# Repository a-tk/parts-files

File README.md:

# parts-files
A place to store project files and to make those available to the world

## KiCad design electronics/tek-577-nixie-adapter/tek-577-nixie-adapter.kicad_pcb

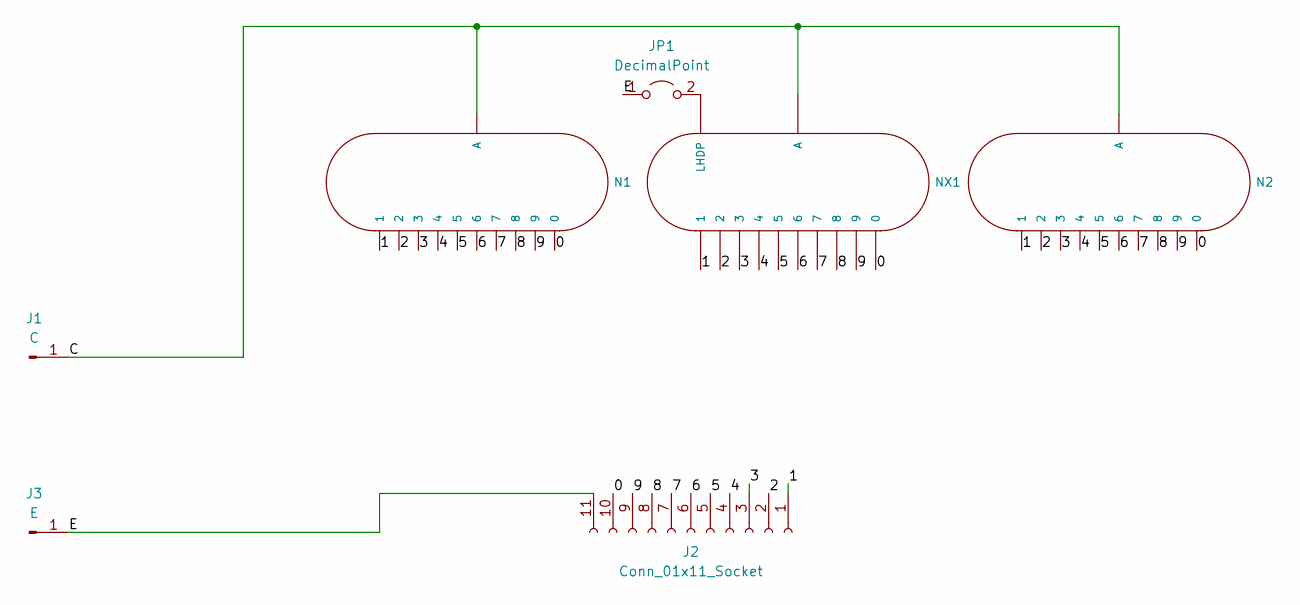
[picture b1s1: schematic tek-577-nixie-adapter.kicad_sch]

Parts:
J1: C; MountingHole_4mm_Pad_TopBottom
J2: Conn_01x11_Socket; Grayhill Single Pole 10 Position Switch
J3: E; MountingHole_4mm_Pad_TopBottom
JP1: DecimalPoint; TestPoint_2Pads_Pitch2.54mm_Drill0.8mm
N1: IN-4; IN-4-DSUB
N2: IN-2; IN-2-DSUB
NX1: IN-12BIN-12-DSUB; IN-12-DSUB

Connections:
/0: J2.10, N1.0, N2.0, NX1.0
/1: J2.1, N1.1, N2.1, NX1.1
/2: J2.2, N1.2, N2.2, NX1.2
/3: J2.3, N1.3, N2.3, NX1.3
/4: J2.4, N1.4, N2.4, NX1.4
/5: J2.5, N1.5, N2.5, NX1.5
/6: J2.6, N1.6, N2.6, NX1.6
/7: J2.7, N1.7, N2.7, NX1.7
/8: J2.8, N1.8, N2.8, NX1.8
/9: J2.9, N1.9, N2.9, NX1.9
/C: J1.1, N1.A3 (A), N2.A, NX1.A
/E: J2.11, J3.1, JP1.1 (A)
unnamed: JP1.2 (B), NX1.LHDP

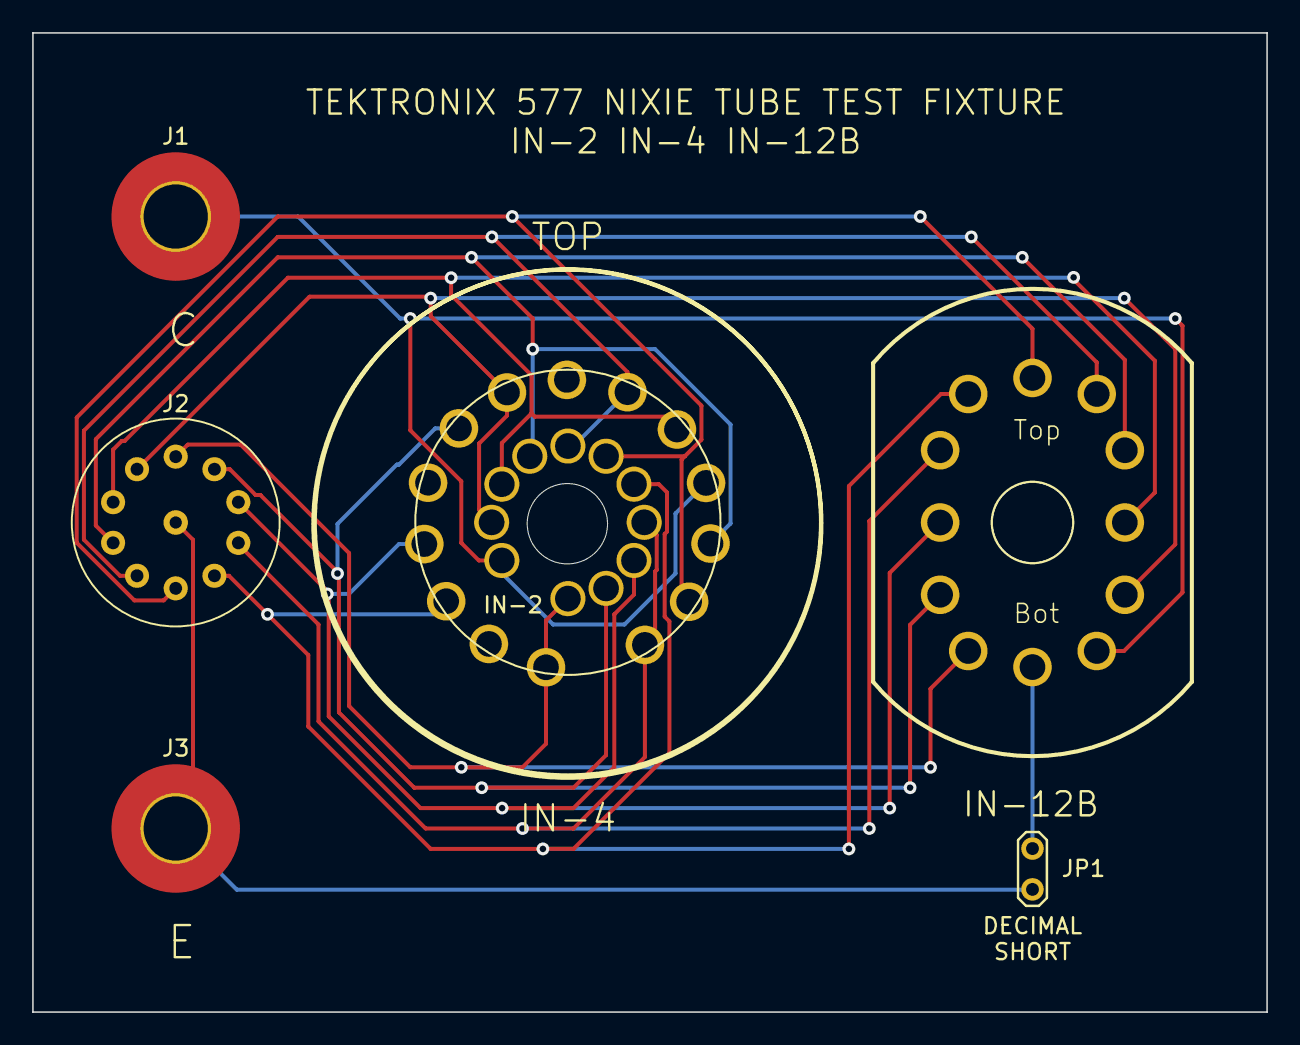
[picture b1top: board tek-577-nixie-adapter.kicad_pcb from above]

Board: 2 copper layers, 76.8 x 61.0 mm, 7 parts (0 on the bottom side), 13 nets.

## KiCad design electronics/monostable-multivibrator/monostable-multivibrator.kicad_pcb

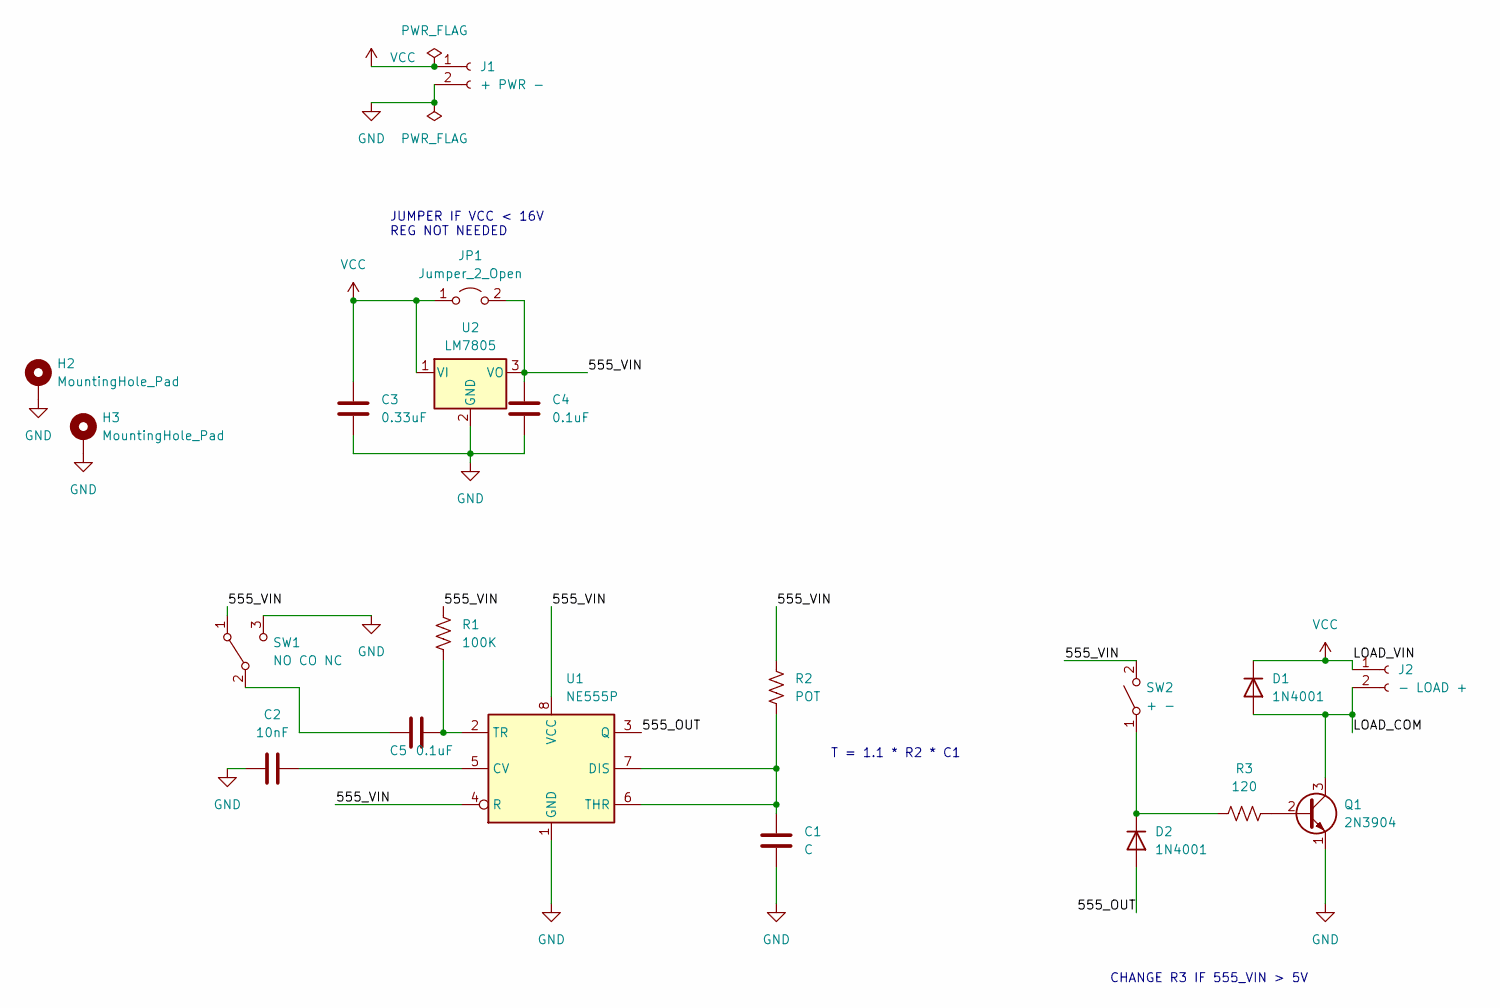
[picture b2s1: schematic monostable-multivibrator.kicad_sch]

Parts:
C1: C; CP_Radial_D8.0mm_P3.80mm
C2: 10nF; C_Disc_D4.3mm_W1.9mm_P5.00mm
C3: 0.33uF; C_Disc_D4.3mm_W1.9mm_P5.00mm
C4, C5: 0.1uF; C_Disc_D4.3mm_W1.9mm_P5.00mm
D1, D2: 1N4001; D_DO-41_SOD81_P10.16mm_Horizontal
H2, H3: MountingHole_Pad; MountingHole_3.2mm_M3_DIN965_Pad_TopBottom
J1: + PWR -; PinSocket_1x02_P2.54mm_Vertical
J2: - LOAD +; PinSocket_1x02_P2.54mm_Vertical
JP1: Jumper_2_Open; R_Axial_DIN0207_L6.3mm_D2.5mm_P2.54mm_Vertical
Q1: 2N3904; TO-92
R1: 100K; R_Axial_DIN0207_L6.3mm_D2.5mm_P7.62mm_Horizontal
R2: POT; R_Axial_DIN0207_L6.3mm_D2.5mm_P7.62mm_Horizontal
R3: 120; R_Axial_DIN0207_L6.3mm_D2.5mm_P7.62mm_Horizontal
SW1: NO CO NC; PinHeader_1x03_P2.54mm_Vertical
SW2: + -; PinHeader_1x02_P2.54mm_Vertical
U1: NE555P; DIP-8_W7.62mm
U2: LM7805; TO-220-3_Vertical

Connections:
/555_OUT: D2.2 (A), U1.3 (Q)
/555_VIN: C4.1, JP1.2 (B), R1.1, R2.1, SW1.1 (A), SW2.2 (B), U1.4 (R), U1.8 (VCC), U2.3 (VO)
/LOAD_COM: D1.2 (A), J2.2, Q1.3 (C)
GND: C1.2, C2.1, C3.2, C4.2, H2.1, H3.1, J1.2, Q1.1 (E), SW1.3 (C), U1.1 (GND), U2.2 (GND)
unnamed: D2.1 (K), R3.1, SW2.1 (A)
unnamed: Q1.2 (B), R3.2
unnamed: C5.2, SW1.2 (B)
unnamed: C2.2, U1.5 (CV)
unnamed: C1.1, R2.2, U1.6 (THR), U1.7 (DIS)
unnamed: C5.1, R1.2, U1.2 (TR)
VCC: C3.1, D1.1 (K), J1.1, J2.1, JP1.1 (A), U2.1 (VI)

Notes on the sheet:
CHANGE R3 IF 555_VIN > 5V
JUMPER IF VCC < 16V REG NOT NEEDED
T = 1.1 * R2 * C1

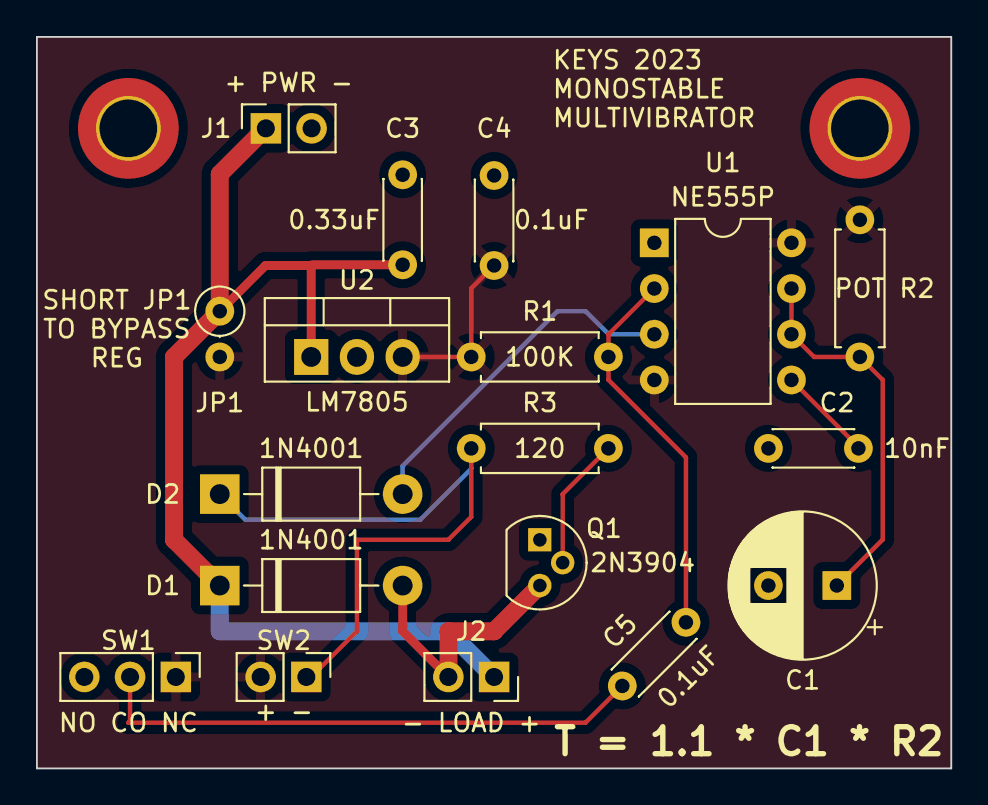
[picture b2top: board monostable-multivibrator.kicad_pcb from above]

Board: 2 copper layers, 50.8 x 40.6 mm, 20 parts (0 on the bottom side), 11 nets.

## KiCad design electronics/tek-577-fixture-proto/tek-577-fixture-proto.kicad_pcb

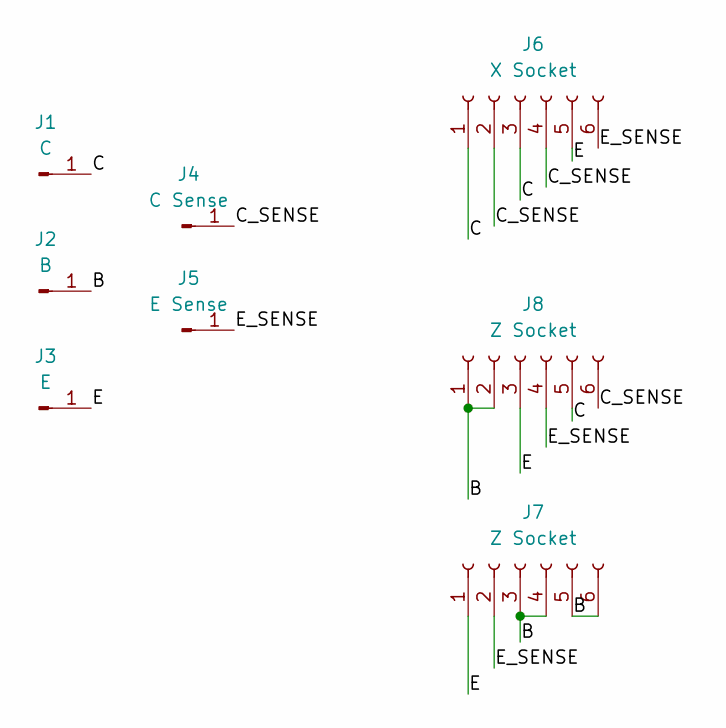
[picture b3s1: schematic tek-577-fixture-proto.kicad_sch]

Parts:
J1: C; MountingHole_4mm_Pad_TopBottom
J2: B; MountingHole_4mm_Pad_TopBottom
J3: E; MountingHole_4mm_Pad_TopBottom
J4: C Sense; MountingHole_4mm_Pad_TopBottom
J5: E Sense; MountingHole_4mm_Pad_TopBottom
J6: X Socket; PinSocket_1x06_P2.54mm_Vertical
J7, J8: Z Socket; PinSocket_1x06_P2.54mm_Vertical

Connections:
/B: J2.1, J7.3, J7.4, J7.5, J7.6, J8.1, J8.2
/C: J1.1, J6.1, J6.3, J8.5
/C_SENSE: J4.1, J6.2, J6.4, J8.6
/E: J3.1, J6.5, J7.1, J8.3
/E_SENSE: J5.1, J6.6, J7.2, J8.4

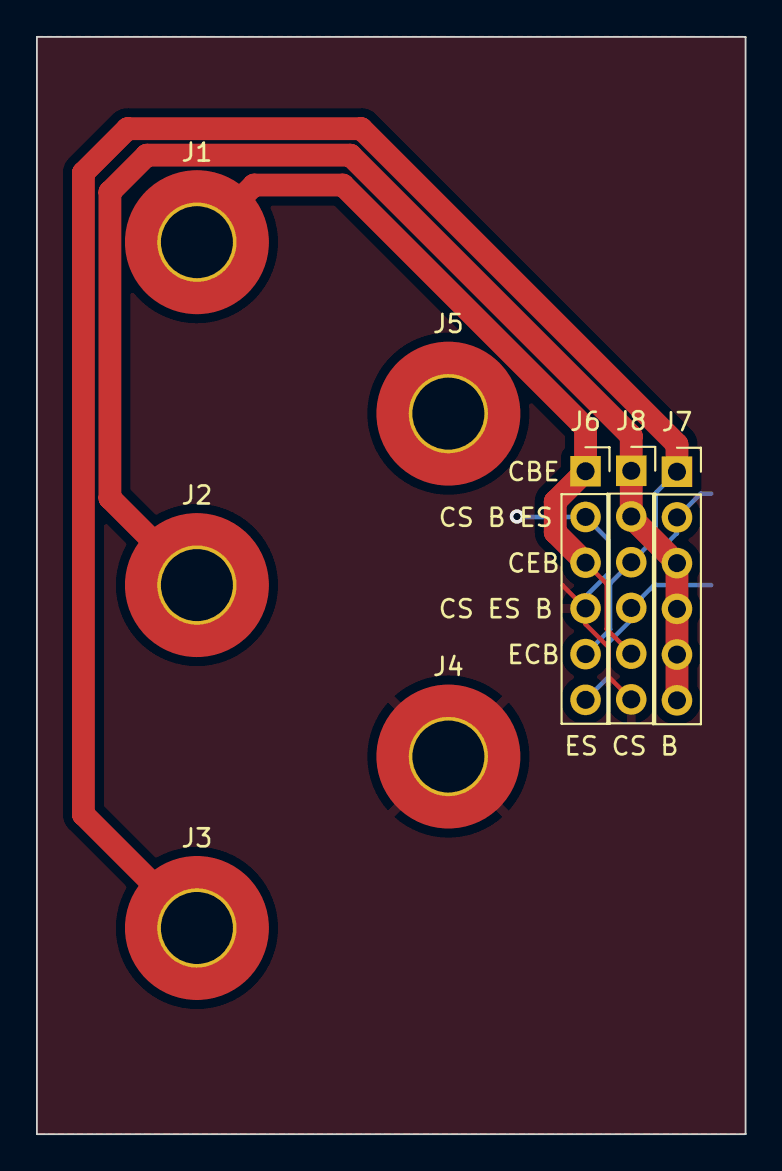
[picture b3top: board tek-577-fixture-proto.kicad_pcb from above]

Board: 2 copper layers, 39.4 x 61.0 mm, 8 parts (0 on the bottom side), 5 nets.

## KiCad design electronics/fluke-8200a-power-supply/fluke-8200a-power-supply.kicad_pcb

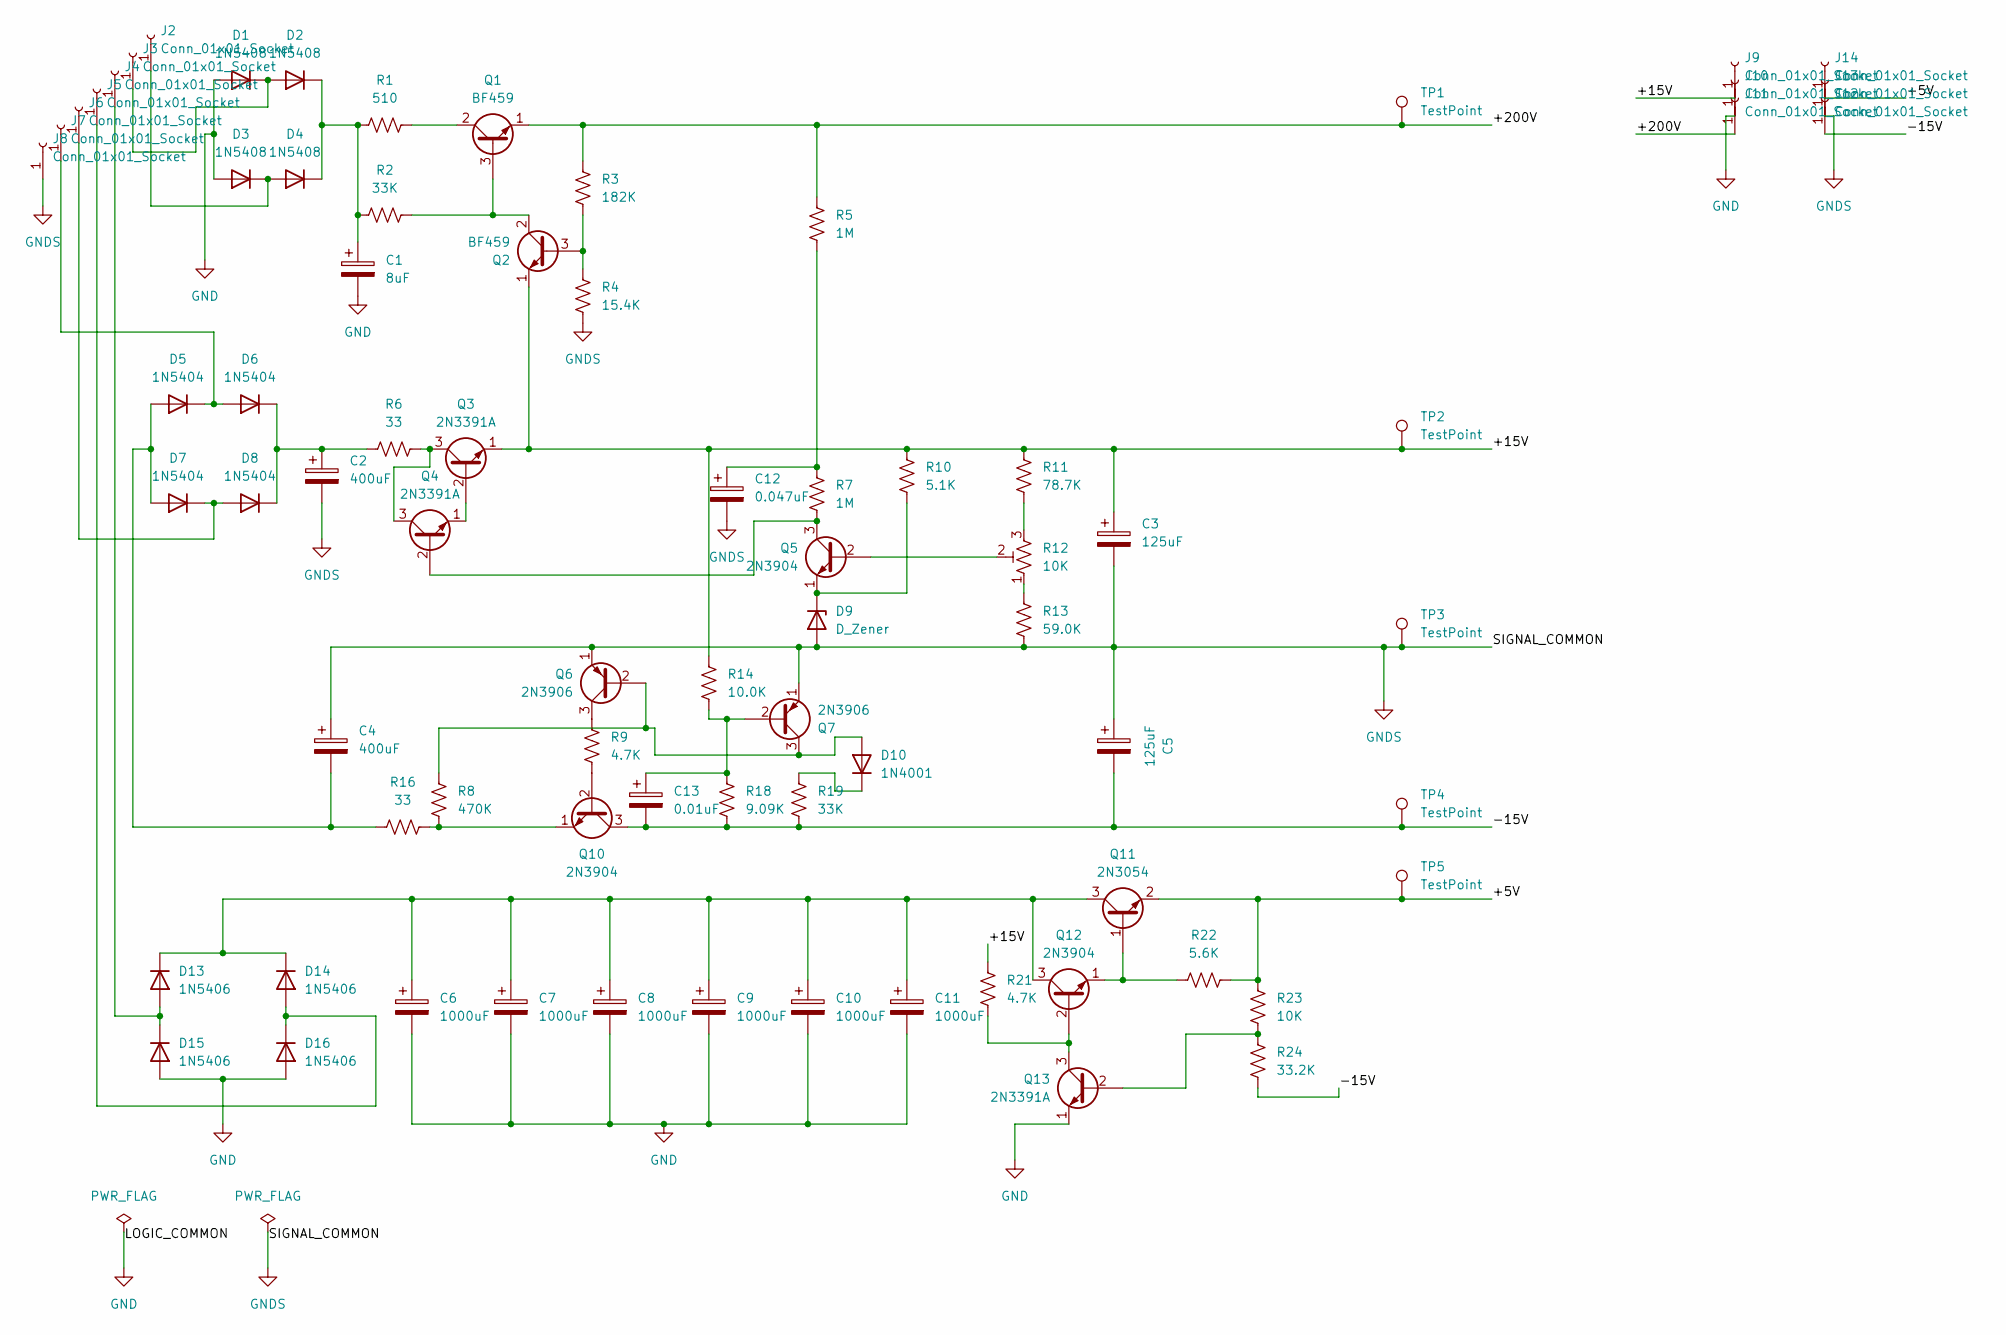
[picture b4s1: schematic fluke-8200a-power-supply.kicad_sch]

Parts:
C1: 8uF; CP_Axial_L37.0mm_D13.0mm_P43.00mm_Horizontal
C2, C4: 400uF; CP_Axial_L30.0mm_D10.0mm_P35.00mm_Horizontal
C3, C5: 125uF; CP_Axial_L18.0mm_D8.0mm_P25.00mm_Horizontal
C6, C7, C8, C9, C10, C11: 1000uF; CP_Axial_L30.0mm_D10.0mm_P35.00mm_Horizontal
C12: 0.047uF; C_Rect_L13.0mm_W4.0mm_P10.00mm_FKS3_FKP3_MKS4
C13: 0.01uF; C_Disc_D8.0mm_W2.5mm_P5.00mm
D1, D2, D3, D4: 1N5408; D_DO-201AD_P15.24mm_Horizontal
D5, D6, D7, D8: 1N5404; D_DO-201AD_P15.24mm_Horizontal
D9: D_Zener; D_A-405_P12.70mm_Horizontal
D10: 1N4001; D_DO-41_SOD81_P12.70mm_Horizontal
D13, D14, D15, D16: 1N5406; D_DO-201AD_P15.24mm_Horizontal
J2, J3, J4, J5, J6, J7, J8, J9, J10, J11, J12, J13, J14: Conn_01x01_Socket; PinSocket_1x01_P2.54mm_Vertical
Q1, Q2: BF459; TO-126-3_Vertical
Q3, Q4, Q13: 2N3391A; TO-92_Inline
Q5, Q10, Q12: 2N3904; TO-92_Inline
Q6, Q7: 2N3906; TO-92_Inline
Q11: 2N3054; TO66
R1: 510; R_Axial_DIN0614_L14.3mm_D5.7mm_P15.24mm_Horizontal
R2, R19: 33K; R_Axial_DIN0309_L9.0mm_D3.2mm_P12.70mm_Horizontal
R3: 182K; R_Axial_DIN0309_L9.0mm_D3.2mm_P12.70mm_Horizontal
R4: 15.4K; R_Axial_DIN0309_L9.0mm_D3.2mm_P12.70mm_Horizontal
R5, R7: 1M; R_Axial_DIN0309_L9.0mm_D3.2mm_P12.70mm_Horizontal
R6, R16: 33; R_Axial_DIN0309_L9.0mm_D3.2mm_P12.70mm_Horizontal
R8: 470K; R_Axial_DIN0309_L9.0mm_D3.2mm_P12.70mm_Horizontal
R9, R21: 4.7K; R_Axial_DIN0309_L9.0mm_D3.2mm_P12.70mm_Horizontal
R10: 5.1K; R_Axial_DIN0309_L9.0mm_D3.2mm_P12.70mm_Horizontal
R11: 78.7K; R_Axial_DIN0309_L9.0mm_D3.2mm_P12.70mm_Horizontal
R12: 10K; Potentiometer_Runtron_RM-063_Horizontal
R13: 59.0K; R_Axial_DIN0309_L9.0mm_D3.2mm_P12.70mm_Horizontal
R14: 10.0K; R_Axial_DIN0309_L9.0mm_D3.2mm_P12.70mm_Horizontal
R18: 9.09K; R_Axial_DIN0309_L9.0mm_D3.2mm_P12.70mm_Horizontal
R22: 5.6K; R_Axial_DIN0309_L9.0mm_D3.2mm_P12.70mm_Horizontal
R23: 10K; R_Axial_DIN0309_L9.0mm_D3.2mm_P12.70mm_Horizontal
R24: 33.2K; R_Axial_DIN0309_L9.0mm_D3.2mm_P12.70mm_Horizontal
TP1, TP2, TP3, TP4, TP5: TestPoint; TestPoint_Loop_D3.50mm_Drill0.9mm_Beaded

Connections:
/+5V: J14.1, Q11.2 (E), R22.2, R23.2, TP5.1
/+15V: C3.1, J9.1, Q2.1 (E), Q3.1 (E), R10.1, R11.1, R14.1, R21.2, TP2.1
/+200V: J11.1, Q1.1 (E), R3.2, R5.1, TP1.1
/-15V: C5.2, C13.2, J12.1, Q10.3 (C), R18.1, R19.1, R24.1, TP4.1
GND: C1.2, C6.2, C7.2, C8.2, C9.2, C10.2, C11.2, D1.2 (A), D3.2 (A), D15.2 (A), D16.2 (A), J10.1, Q13.1 (E)
GNDS: C2.2, C3.2, C4.1, C5.1, C12.2, D9.2 (A), J8.1, J13.1, Q6.1 (E), Q7.1 (E), R4.1, R13.2, TP3.1
unnamed: C12.1, R5.2, R7.1
unnamed: D1.1 (K), D2.2 (A), J3.1
unnamed: C1.1, D2.1 (K), D4.1 (K), R1.1, R2.1
unnamed: D3.1 (K), D4.2 (A), J2.1
unnamed: C4.2, D5.2 (A), D7.2 (A), R16.1
unnamed: D5.1 (K), D6.2 (A), J7.1
unnamed: C2.1, D6.1 (K), D8.1 (K), R6.1
unnamed: D7.1 (K), D8.2 (A), J6.1
unnamed: D9.1 (K), Q5.1 (E), R10.2
unnamed: D10.2 (A), Q6.2 (B), Q7.3 (C), R8.1
unnamed: D10.1 (K), R19.2
unnamed: D13.2 (A), D15.1 (K), J4.1
unnamed: C6.1, C7.1, C8.1, C9.1, C10.1, C11.1, D13.1 (K), D14.1 (K), Q11.3 (C), Q12.3 (C)
unnamed: D14.2 (A), D16.1 (K), J5.1
unnamed: Q1.3 (B), Q2.2 (C), R2.2
unnamed: Q1.2 (C), R1.2
unnamed: Q2.3 (B), R3.1, R4.2
unnamed: Q3.2 (B), Q4.1 (E)
unnamed: Q3.3 (C), Q4.3 (C), R6.2
unnamed: Q4.2 (B), Q5.3 (C), R7.2
unnamed: Q5.2 (B), R12.2
unnamed: Q6.3 (C), R9.1
unnamed: C13.1, Q7.2 (B), R14.2, R18.2
unnamed: Q10.2 (B), R9.2
unnamed: Q10.1 (E), R8.2, R16.2
unnamed: Q11.1 (B), Q12.1 (E), R22.1
unnamed: Q12.2 (B), Q13.3 (C), R21.1
unnamed: Q13.2 (B), R23.1, R24.2
unnamed: R11.2, R12.3
unnamed: R12.1, R13.1

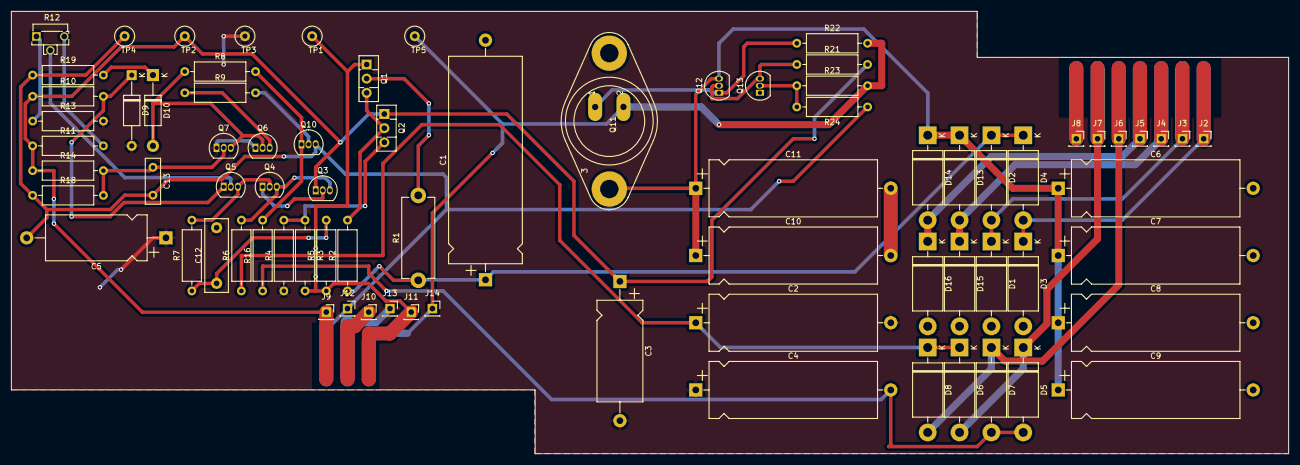
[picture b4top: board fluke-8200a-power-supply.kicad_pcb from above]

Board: 2 copper layers, 229.2 x 79.4 mm, 77 parts (0 on the bottom side), 36 nets.

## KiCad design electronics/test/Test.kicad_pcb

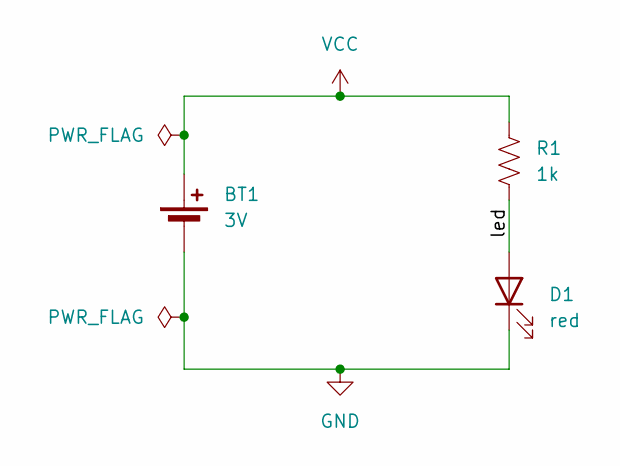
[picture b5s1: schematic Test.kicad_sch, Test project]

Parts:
BT1: 3V; BatteryHolder_Keystone_1058_1x2032
D1: red; LED_D5.0mm
R1: 1k; R_Axial_DIN0309_L9.0mm_D3.2mm_P12.70mm_Horizontal

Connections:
/led: D1.2 (A), R1.2
GND: BT1.2 (-), D1.1 (K)
VCC: BT1.1 (+), R1.1

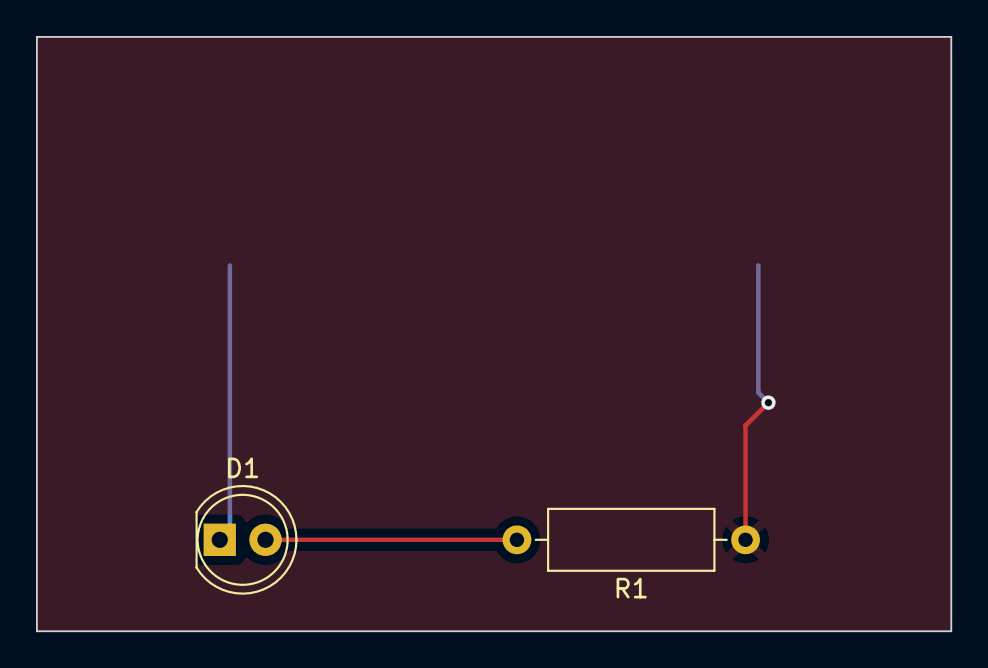
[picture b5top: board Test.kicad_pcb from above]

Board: 2 copper layers, 50.8 x 33.0 mm, 3 parts (1 on the bottom side), 3 nets.

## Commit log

2023-03-16 Adding directory
2023-04-13 Adding drawing for Shars conversion
2023-06-10 adding electonics file and basic kicad project
2023-06-11 adding tutorial directory
2023-06-11 finished tutorial
2023-06-11 adding basic schematic
2023-06-11 adding more components
2023-06-11 more updates
2023-06-11 mostly finished
2023-06-12 footprints
2023-06-12 adjustments
2023-06-12 looking finished
2023-06-13 adding important note
2023-06-13 adding test project. Abandoning this method, moving to schematic match
2023-06-13 only need correct transistors now
2023-06-13 changed to pin headers
2023-06-13 PCB work.
2023-06-14 PCB quotable, but not yet fully compatable with fluke 8200A
2023-06-15 adding new project
2023-06-21 boilerplate
2023-06-21 adding symbols
2023-06-21 working footprints
2023-06-22 adding library references and cleanup
2023-06-22 adding other tubes
2023-06-22 adding switch and schematic done
2023-06-22 adding the footprints, which only loaded on mac for some reason
2023-06-22 board design done
2023-06-22 routing improvements
2023-06-25 nice silkscreen updates
2023-06-25 added cap to fix repeated triggers
2023-06-25 bug fix, held button should no longer keep switch active.
2023-07-09 fixing decimal point short with jumper
2023-07-27 fixing switch spacing, fixing 100nF to 0.1uF
